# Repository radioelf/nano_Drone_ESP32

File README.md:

PCB con Kicad  para placa de un nano dron utilizando un ESP32 y un módulo GY-91 MPU9250 + BMP280. Usando el firmware de https://github.com/rtlopez/esp-fc (Gran trabajo, gracias).

Kicad PCB for the board of a nano drone using an ESP32 and a GY-91 MPU9250 + BMP280 module. Using the firmware from https://github.com/rtlopez/esp-fc (Great job, thanks).

Creative Commons License Disclaimer

UNLESS OTHERWISE MUTUALLY AGREED TO BY THE PARTIES IN WRITING, LICENSOR OFFERS THE WORK AS-IS AND MAKES NO REPRESENTATIONS OR WARRANTIES OF ANY KIND CONCERNING THE WORK, EXPRESS, IMPLIED, STATUTORY OR OTHERWISE, INCLUDING, WITHOUT LIMITATION, WARRANTIES OF TITLE, MERCHANTIBILITY, FITNESS FOR A PARTICULAR PURPOSE, NONINFRINGEMENT, OR THE ABSENCE OF LATENT OR OTHER DEFECTS, ACCURACY, OR THE PRESENCE OF ABSENCE OF ERRORS, WHETHER OR NOT DISCOVERABLE. SOME JURISDICTIONS DO NOT ALLOW THE EXCLUSION OF IMPLIED WARRANTIES, SO SUCH EXCLUSION MAY NOT APPLY TO YOU. EXCEPT TO THE EXTENT REQUIRED BY APPLICABLE LAW, IN NO EVENT WILL LICENSOR BE LIABLE TO YOU ON ANY LEGAL THEORY FOR ANY SPECIAL, INCIDENTAL, CONSEQUENTIAL, PUNITIVE OR EXEMPLARY DAMAGES ARISING OUT OF THIS LICENSE OR THE USE OF THE WORK, EVEN IF LICENSOR HAS BEEN ADVISED OF THE POSSIBILITY OF SUCH DAMAGES.

http://creativecommons.org/licenses/by-sa/3.0/

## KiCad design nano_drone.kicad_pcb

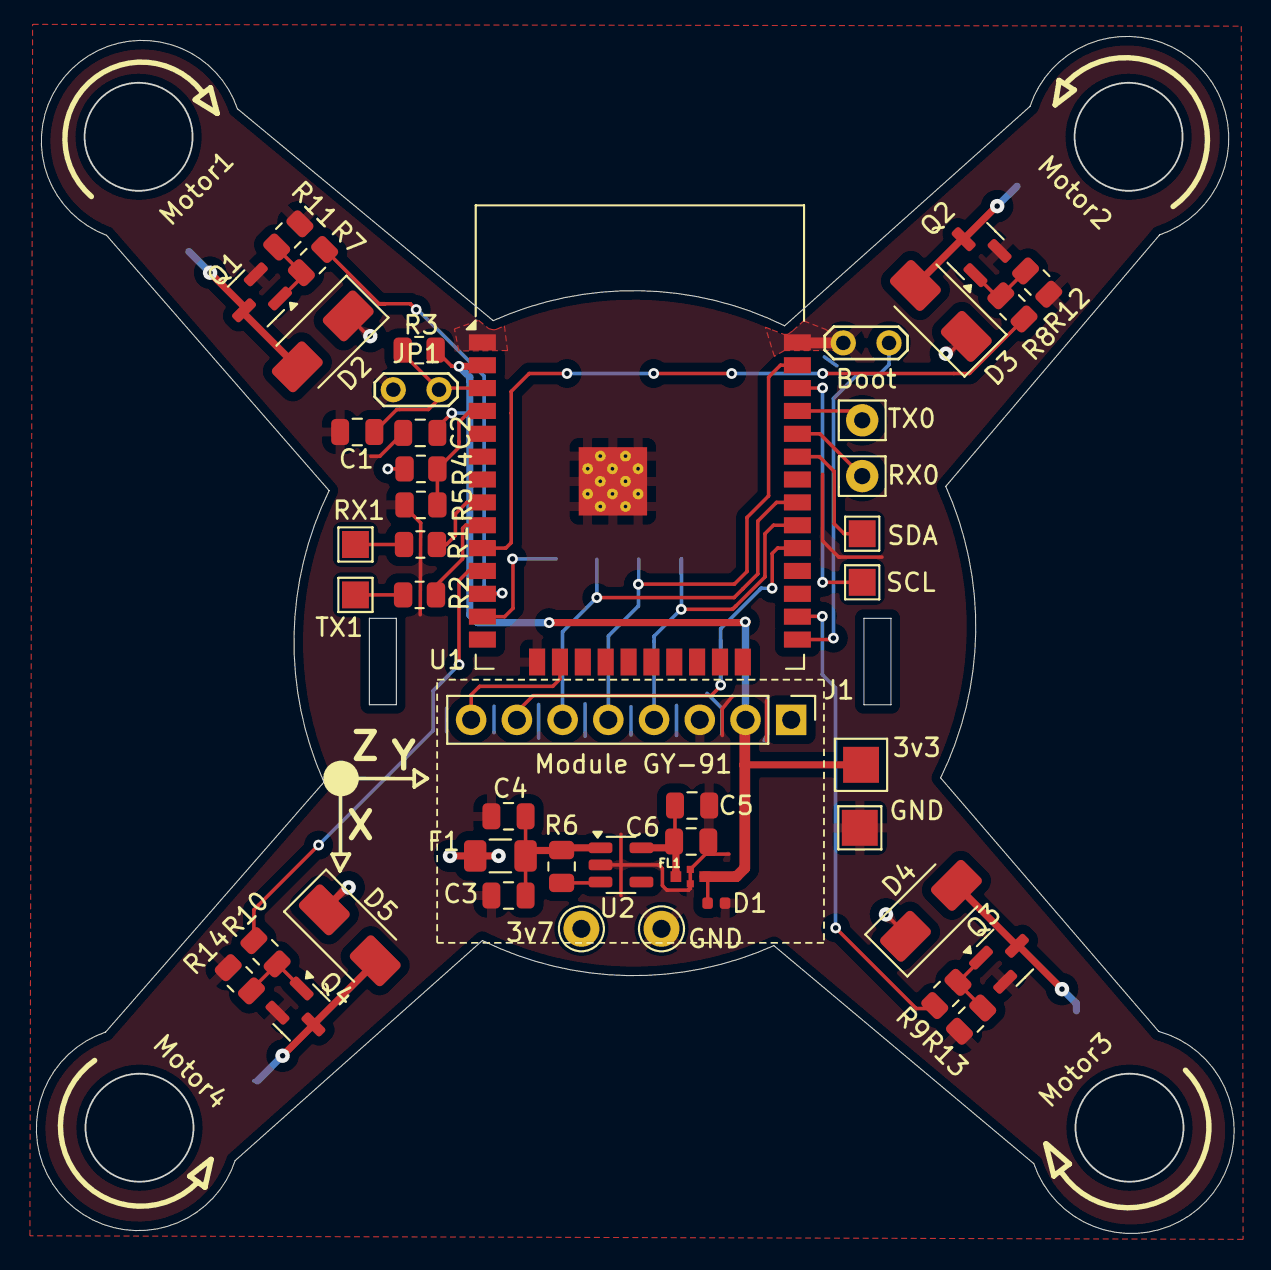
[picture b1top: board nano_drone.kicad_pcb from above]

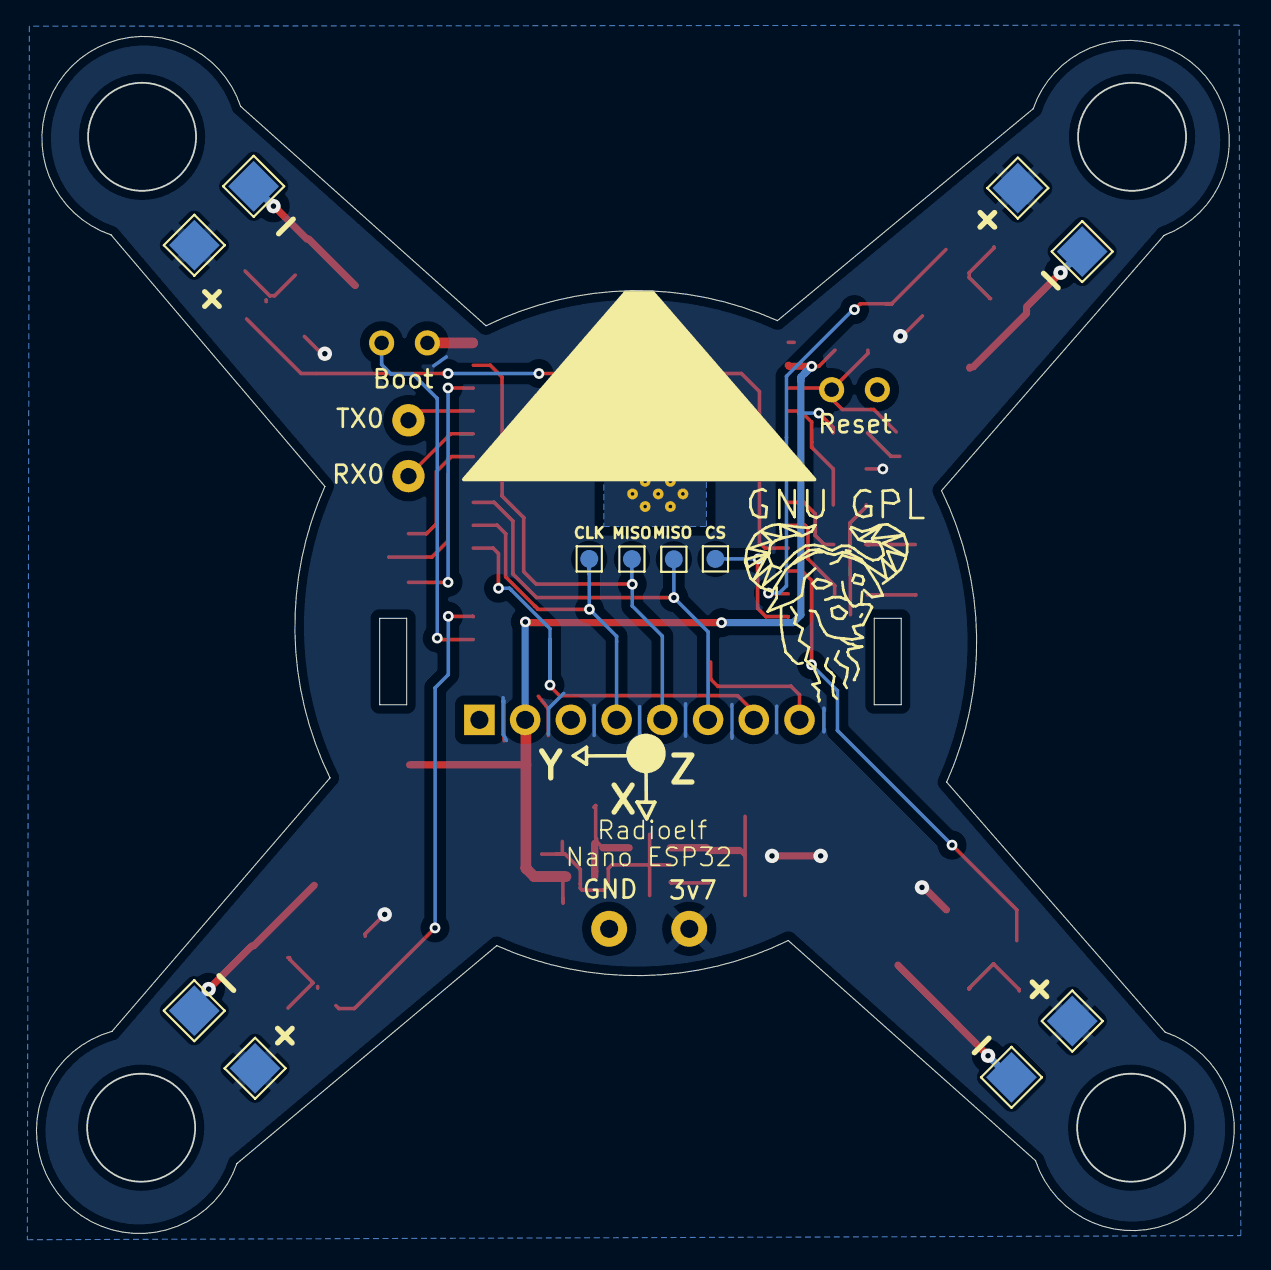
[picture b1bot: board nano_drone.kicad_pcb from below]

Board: 2 copper layers, 66.5 x 66.5 mm, 54 parts (8 on the bottom side), 34 nets.

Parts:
C1: 1uF; C_0805_2012Metric
C2, C3, C5: 100nF; C_0805_2012Metric
C4, C6: 10uF; C_0805_2012Metric
D1: PESD0402-140; L_0402_1005Metric
D2, D3, D4, D5: STPS1L30A; D_SMA
F1: 0ZCA0035FF2G; Fuse_1206_3216Metric
FL1: KNH16C104DA5TS; FIL_KNH16C104DA5TS
H1: GND; Pin_D1.0mm_L10.0mm
H2: 3v7; Pin_D1.0mm_L10.0mm
H3: TX0; Pin_D0.9mm_L10.0mm_W2.4mm_FlatFork
H4: RX0; Pin_D0.9mm_L10.0mm_W2.4mm_FlatFork
J1: Module GY-91 MPU9250 + BMP280; PinHeader_1x08_P2.54mm_Vertical
JP1: Reset; TestPoint_2Pads_Pitch2.54mm_Drill0.8mm
JP2: Boot; TestPoint_2Pads_Pitch2.54mm_Drill0.8mm
Q1, Q2, Q3, Q4: DMG3404L; SOT-23
R1, R2: 120R; R_0805_2012Metric
R3: 10k; R_0805_2012Metric
R4: 150k; R_0805_2012Metric
R5: 220k; R_0805_2012Metric
R6: 10K; R_0805_2012Metric
R7, R8, R9, R10: 1k; R_0805_2012Metric
R11, R12, R13, R14: 100k; R_0805_2012Metric
TP1: GND; TestPoint_Pad_2.0x2.0mm
TP2: RX1; TestPoint_Pad_1.5x1.5mm
TP3: TX1; TestPoint_Pad_1.5x1.5mm
TP4: SDA; TestPoint_Pad_1.5x1.5mm
TP5: SCL; TestPoint_Pad_1.5x1.5mm
TP6: 3v3; TestPoint_Pad_2.5x2.5mm
TP7, TP12, TP13, TP14: 3v7; TestPoint_Pad_2.0x2.0mm
TP8: Motor1; TestPoint_Pad_2.0x2.0mm
TP9: Motor2; TestPoint_Pad_2.0x2.0mm
TP10: Motor3; TestPoint_Pad_2.0x2.0mm
TP11: Motor4; TestPoint_Pad_2.0x2.0mm
U1: ESP32-WROOM-32E; ESP32-WROOM-32D
U2: XC6220B331MR-G; SOT-23-5

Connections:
+3v3: C2.2, D1.1 (C), FL1.2, J1.2, R3.1, TP6.1, U1.2 (VDD)
ADC_VOLTAGE: R4.2, R5.1, U1.4 (SENSOR_VP)
GND: C1.1, C2.1, C3.2, C4.2, C5.2, C6.2, D1.2 (A), FL1.3, FL1.4, H1.1, J1.3, JP1.1 (A), JP2.1 (A), Q1.2 (S), Q2.2 (S), Q3.2 (S), Q4.2 (S), R5.2, R11.1, R12.1, R13.1, R14.1, TP1.1, U1.1 (GND), U1.15 (GND), U1.38 (GND), U1.39 (GND), U2.2 (GND)
I2C0_SCL: TP5.1, U1.36 (IO22)
I2C0_SDA: TP4.1, U1.33 (IO21)
unnamed: D2.2 (A), Q1.3 (D), TP8.1
unnamed: D3.2 (A), Q2.3 (D), TP9.1
unnamed: D4.2 (A), Q3.3 (D), TP10.1
unnamed: D5.2 (A), Q4.3 (D), TP11.1
unnamed: C1.2, JP1.2 (B), R3.2, U1.3 (EN)
unnamed: JP2.2 (B), U1.25 (IO0)
unnamed: Q1.1 (G), R7.2, R11.2
unnamed: Q2.1 (G), R8.2, R12.2
unnamed: Q3.1 (G), R9.2, R13.2
unnamed: Q4.1 (G), R10.2, R14.2
unnamed: R1.2, TP2.1
unnamed: R2.2, TP3.1
unnamed: R6.2, U2.3 (EN)
unnamed: C3.1, C4.1, F1.2, R6.1, U2.1 (VIN)
unnamed: C5.1, C6.1, FL1.1, U2.5 (VOUT)
PWM1: R7.1, U1.12 (IO27)
PWM2: R8.1, U1.10 (IO25)
PWM3: R9.1, U1.26 (IO4)
PWM4: R10.1, U1.11 (IO26)
RX0: H4.1, U1.34 (RXD0/IO3)
RX1: R1.1, U1.8 (IO32)
SPI0_CLK: J1.4, U1.30 (IO18)
SPI0_CS0_M: J1.7, U1.29 (IO5)
SPI0_CS1_B: J1.8, U1.16 (IO13)
SPI0_MISO: J1.6, U1.31 (IO19)
SPI0_MOSI: J1.5, U1.37 (IO23)
TX0: H3.1, U1.35 (TXD0/IO1)
TX1: R2.1, U1.9 (IO33)
VDD_3v7: D2.1 (K), D3.1 (K), D4.1 (K), D5.1 (K), F1.1, H2.1, R4.1, TP7.1, TP12.1, TP13.1, TP14.1

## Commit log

2025-03-12 Create gerber
2025-03-12 Create Rename
